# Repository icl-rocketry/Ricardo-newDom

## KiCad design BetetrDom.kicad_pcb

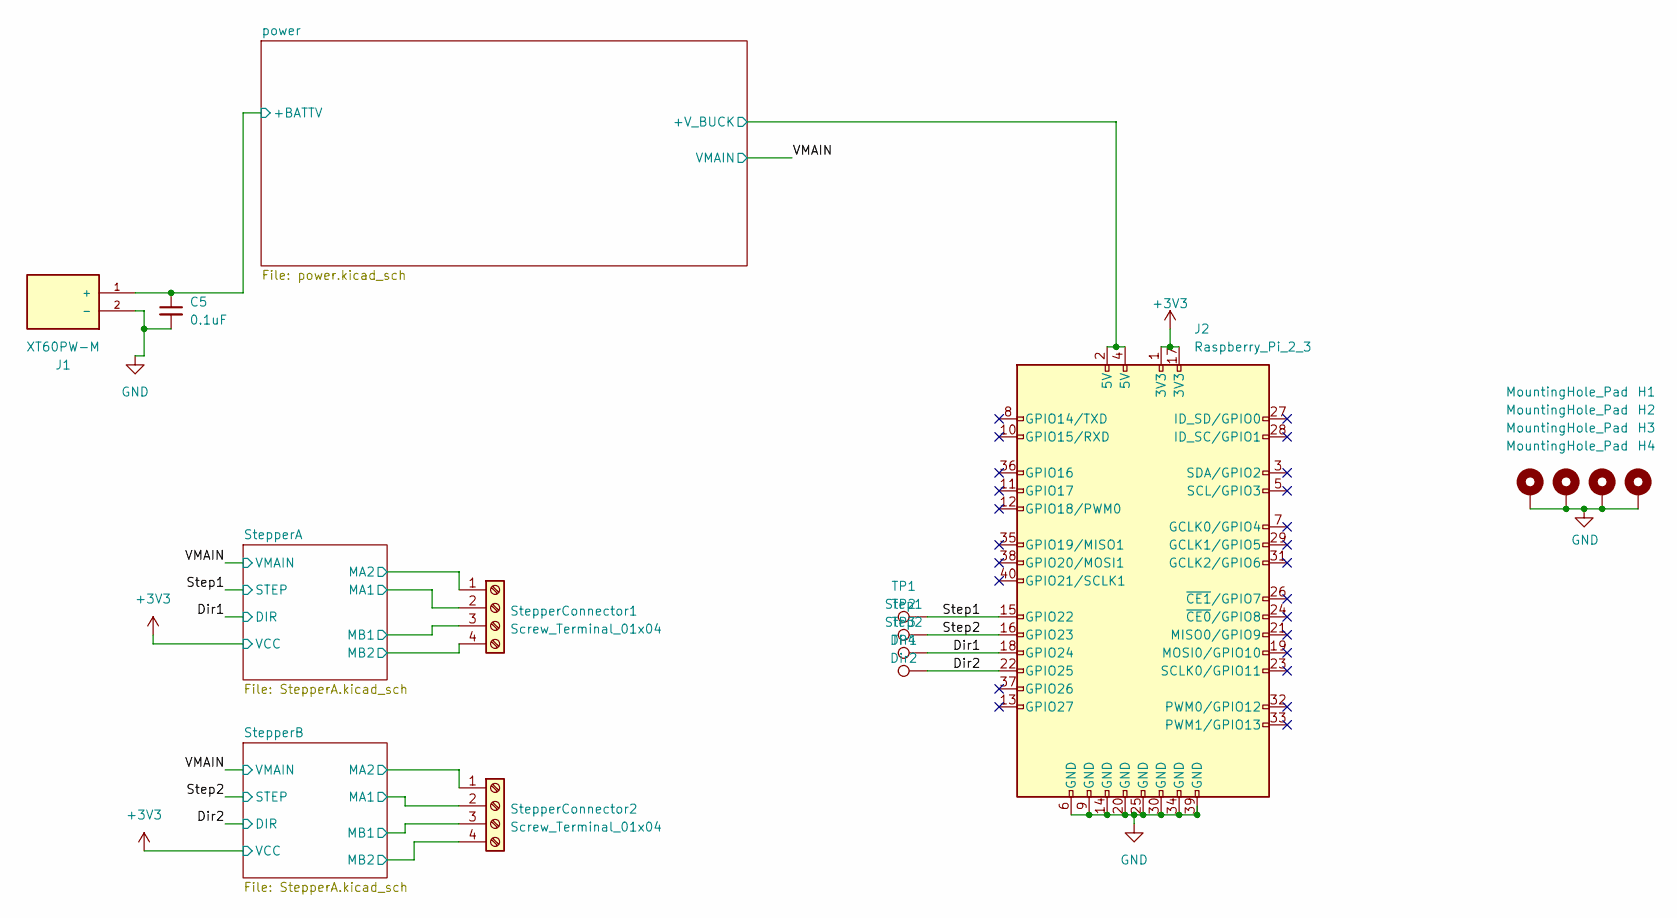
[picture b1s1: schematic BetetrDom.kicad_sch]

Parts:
C5: 0.1uF; C_0402_1005Metric
H1, H2, H3, H4: MountingHole_Pad; MountingHole_3.2mm_M3_DIN965_Pad
J1: XT60PW-M; AMASS_XT60PW-M; PARTREV V1.2
J2: Raspberry_Pi_2_3; PinSocket_2x20_P2.54mm_Vertical
StepperConnector1, StepperConnector2: Screw_Terminal_01x04; Molex_Nano-Fit_105313-xx04_1x04_P2.50mm_Horizontal
TP1: Step1; TestPoint_Pad_1.5x1.5mm
TP2: Step2; TestPoint_Pad_1.5x1.5mm
TP3: Dir1; TestPoint_Pad_1.5x1.5mm
TP4: Dir2; TestPoint_Pad_1.5x1.5mm

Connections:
+3V3: J2.1 (3V3), J2.17 (3V3); also elsewhere on the board
/Dir1: J2.18 (GPIO24), TP3.1; also elsewhere on the board
/Dir2: J2.22 (GPIO25), TP4.1; also elsewhere on the board
/Step1: J2.15 (GPIO22), TP1.1; also elsewhere on the board
/Step2: J2.16 (GPIO23), TP2.1; also elsewhere on the board
/StepperA/MA1: StepperConnector1.2; also elsewhere on the board
/StepperA/MA2: StepperConnector1.1; also elsewhere on the board
/StepperA/MB1: StepperConnector1.3; also elsewhere on the board
/StepperA/MB2: StepperConnector1.4; also elsewhere on the board
/StepperB/MA1: StepperConnector2.2; also elsewhere on the board
/StepperB/MA2: StepperConnector2.1; also elsewhere on the board
/StepperB/MB1: StepperConnector2.3; also elsewhere on the board
/StepperB/MB2: StepperConnector2.4; also elsewhere on the board
/power/+BATTV: C5.1, J1.1 (+); also elsewhere on the board
/power/+V_BUCK: J2.2 (5V), J2.4 (5V); also elsewhere on the board
GND: C5.2, H1.1, H2.1, H3.1, H4.1, J1.2 (-), J2.6 (GND), J2.9 (GND), J2.14 (GND), J2.20 (GND), J2.25 (GND), J2.30 (GND), J2.34 (GND), J2.39 (GND); also elsewhere on the board

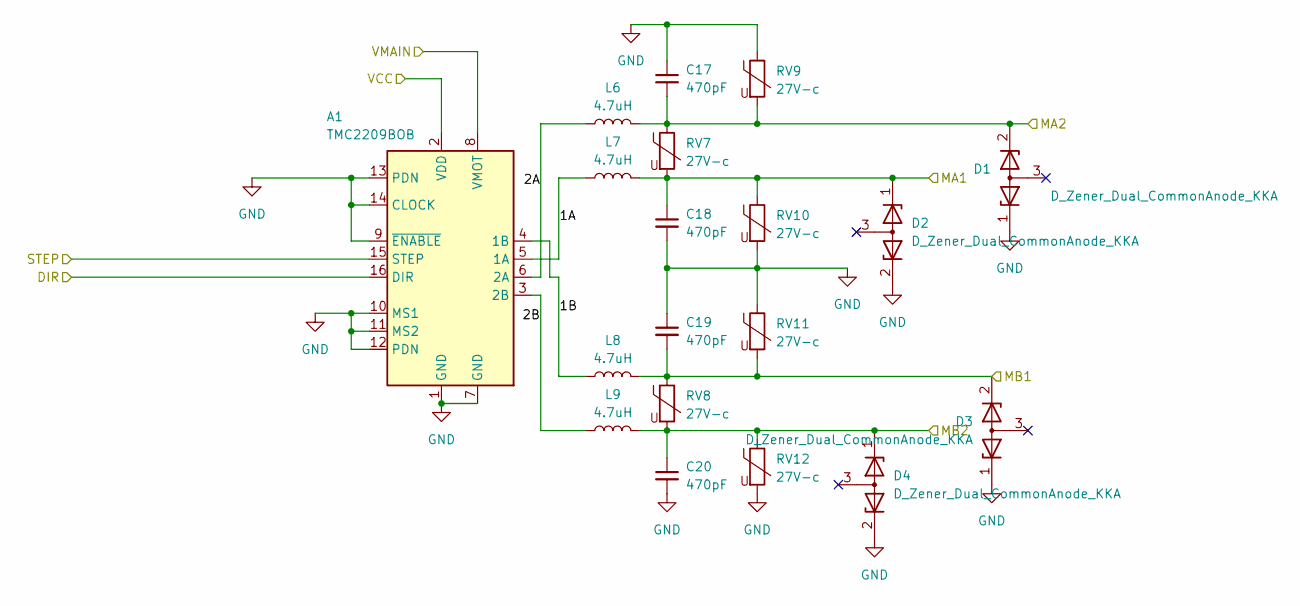
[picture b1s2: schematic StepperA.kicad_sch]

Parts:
A1: TMC2209BOB; Pololu_Breakout-16_15.2x20.3mm
C17, C18, C19, C20: 470pF; C_0603_1608Metric
D1, D2, D3, D4: D_Zener_Dual_CommonAnode_KKA; TSOT-23
L6, L7, L8, L9: 4.7uH; MPLAL60504R7
RV7, RV8, RV9, RV10, RV11, RV12: 27V-c; R_0805_2012Metric

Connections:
+3V3: A1.2 (VDD); also elsewhere on the board
/Dir1: A1.16 (DIR); also elsewhere on the board
/Step1: A1.15 (STEP); also elsewhere on the board
/StepperA/1A: A1.5 (1A), L7.1
/StepperA/1B: A1.4 (1B), L8.1
/StepperA/2A: A1.6 (2A), L6.1
/StepperA/2B: A1.3 (2B), L9.1
/StepperA/MA1: C18.1, D2.1 (K), L7.2, RV7.2, RV10.1; also elsewhere on the board
/StepperA/MA2: C17.2, D1.2 (K), L6.2, RV7.1, RV9.2; also elsewhere on the board
/StepperA/MB1: C19.2, D3.2 (K), L8.2, RV8.1, RV11.2; also elsewhere on the board
/StepperA/MB2: C20.1, D4.1 (K), L9.2, RV8.2, RV12.1; also elsewhere on the board
GND: A1.1 (GND), A1.7 (GND), A1.9 (~ENABLE), A1.10 (MS1), A1.11 (MS2), A1.12 (PDN), A1.13 (PDN), A1.14 (CLOCK), C17.1, C18.2, C19.1, C20.2, D1.1 (K), D2.2 (K), D3.1 (K), D4.2 (K), RV9.1, RV10.2, RV11.1, RV12.2; also elsewhere on the board
VMAIN: A1.8 (VMOT); also elsewhere on the board

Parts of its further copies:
A2: TMC2209BOB; Pololu_Breakout-16_15.2x20.3mm
C13, C14, C15, C16: 470pF; C_0603_1608Metric
D5, D6, D7, D8: D_Zener_Dual_CommonAnode_KKA; TSOT-23
L2, L3, L4, L5: 4.7uH; MPLAL60504R7
RV1, RV2, RV3, RV4, RV5, RV6: 27V-c; R_0805_2012Metric

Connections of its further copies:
+3V3: A2.2 (VDD); also elsewhere on the board
/Dir2: A2.16 (DIR); also elsewhere on the board
/Step2: A2.15 (STEP); also elsewhere on the board
/StepperB/1A: A2.5 (1A), L3.1
/StepperB/1B: A2.4 (1B), L4.1
/StepperB/2A: A2.6 (2A), L2.1
/StepperB/2B: A2.3 (2B), L5.1
/StepperB/MA1: C14.1, D6.1 (K), L3.2, RV1.2, RV4.1; also elsewhere on the board
/StepperB/MA2: C13.2, D5.2 (K), L2.2, RV1.1, RV3.2; also elsewhere on the board
/StepperB/MB1: C15.2, D7.2 (K), L4.2, RV2.1, RV5.2; also elsewhere on the board
/StepperB/MB2: C16.1, D8.1 (K), L5.2, RV2.2, RV6.1; also elsewhere on the board
GND: A2.1 (GND), A2.7 (GND), A2.9 (~ENABLE), A2.10 (MS1), A2.11 (MS2), A2.12 (PDN), A2.13 (PDN), A2.14 (CLOCK), C13.1, C14.2, C15.1, C16.2, D5.1 (K), D6.2 (K), D7.1 (K), D8.2 (K), RV3.1, RV4.2, RV5.1, RV6.2; also elsewhere on the board
VMAIN: A2.8 (VMOT); also elsewhere on the board

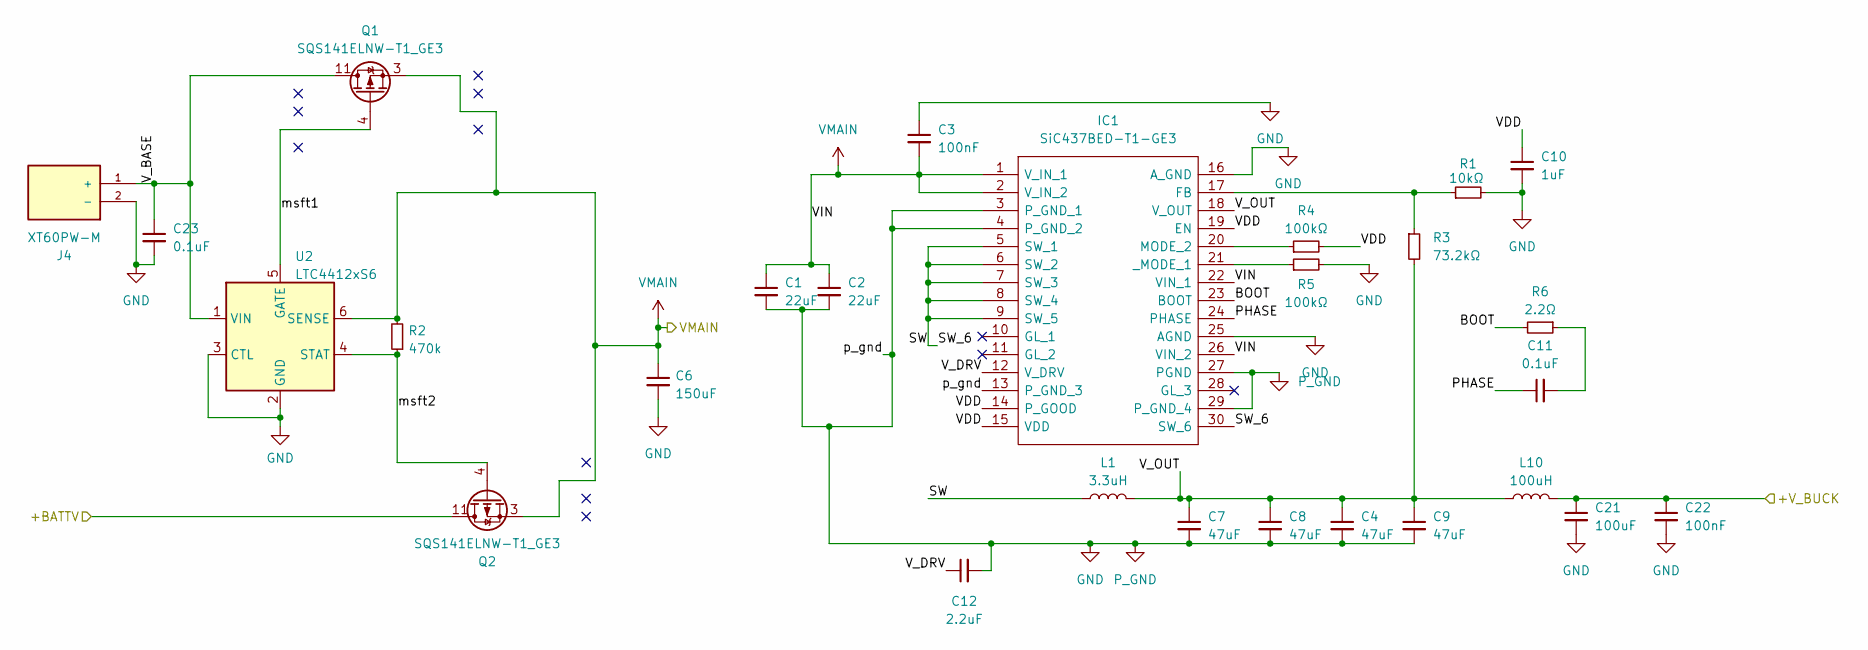
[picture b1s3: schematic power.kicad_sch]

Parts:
C1, C2: 22uF; C_0805_2012Metric
C3, C22: 100nF; C_0402_1005Metric
C4, C7, C8, C9: 47uF; C_1206_3216Metric
C6: 150uF; C_Elec_8x10.2
C10: 1uF; C_0402_1005Metric
C11, C23: 0.1uF; C_0402_1005Metric
C12: 2.2uF; C_0402_1005Metric
C21: 100uF; CP_Elec_10x10
IC1: SiC437BED-T1-GE3; SiC437BEDT1GE3; Manufacturer_Part_Number SiC437BED-T1-GE3; Mouser Part Number 78-SIC437BED-T1-GE3
J4: XT60PW-M; AMASS_XT60PW-M; PARTREV V1.2
L1: 3.3uH; IND_SPM10065VT-3R3M-D
L10: 100uH; SDR1307A101K
Q1, Q2: SQS141ELNW-T1_GE3; SQS850ENT1_GE3; Manufacturer_Part_Number SQS141ELNW-T1_GE3; Mouser Part Number 78-SQS141ELNW-T1_GE3
R1: 10kΩ; R_0402_1005Metric
R2: 470k; R_0603_1608Metric
R3: 73.2kΩ; R_1206_3216Metric
R4, R5: 100kΩ; R_0402_1005Metric
R6: 2.2Ω; R_0402_1005Metric
U2: LTC4412xS6; TSOT-23-6

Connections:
/power/+BATTV: Q2.5, Q2.6, Q2.7, Q2.8, Q2.9, Q2.10, Q2.11; also elsewhere on the board
/power/+V_BUCK: C21.1, C22.1, L10.2; also elsewhere on the board
/power/BOOT: IC1.23 (BOOT), R6.2
/power/PHASE: C11.1, IC1.24 (PHASE)
/power/SW: IC1.5 (SW_1), IC1.6 (SW_2), IC1.7 (SW_3), IC1.8 (SW_4), IC1.9 (SW_5), IC1.30 (SW_6), L1.1
/power/VDD: C10.1, IC1.14 (P_GOOD), IC1.15 (VDD), IC1.19 (EN), R4.2
/power/V_BASE: C23.1, J4.1 (+), Q1.5, Q1.6, Q1.7, Q1.8, Q1.9, Q1.10, Q1.11, U2.1 (VIN)
/power/V_DRV: C12.1, IC1.12 (V_DRV)
/power/V_OUT: C4.1, C7.1, C8.1, C9.1, IC1.18 (V_OUT), L1.2, L10.1, R3.2
/power/msft1: Q1.4, U2.5 (GATE)
/power/msft2: Q2.4, R2.1, U2.4 (STAT)
GND: C1.2, C2.2, C3.1, C4.2, C6.2, C7.2, C8.2, C9.2, C10.2, C12.2, C21.2, C22.2, C23.2, IC1.3 (P_GND_1), IC1.4 (P_GND_2), IC1.13 (P_GND_3), IC1.16 (A_GND), IC1.25 (AGND), IC1.27 (PGND), IC1.29 (P_GND_4), J4.2 (-), R1.2, R5.2, U2.2 (GND), U2.3 (CTL); also elsewhere on the board
unnamed: C11.2, R6.1
unnamed: IC1.17 (FB), R1.1, R3.1
unnamed: IC1.20 (MODE_2), R4.1
unnamed: IC1.21 (_MODE_1), R5.1
VMAIN: C1.1, C2.1, C3.2, C6.1, IC1.1 (V_IN_1), IC1.2 (V_IN_2), IC1.22 (VIN_1), IC1.26 (VIN_2), Q1.1, Q1.2, Q1.3, Q2.1, Q2.2, Q2.3, R2.2, U2.6 (SENSE); also elsewhere on the board

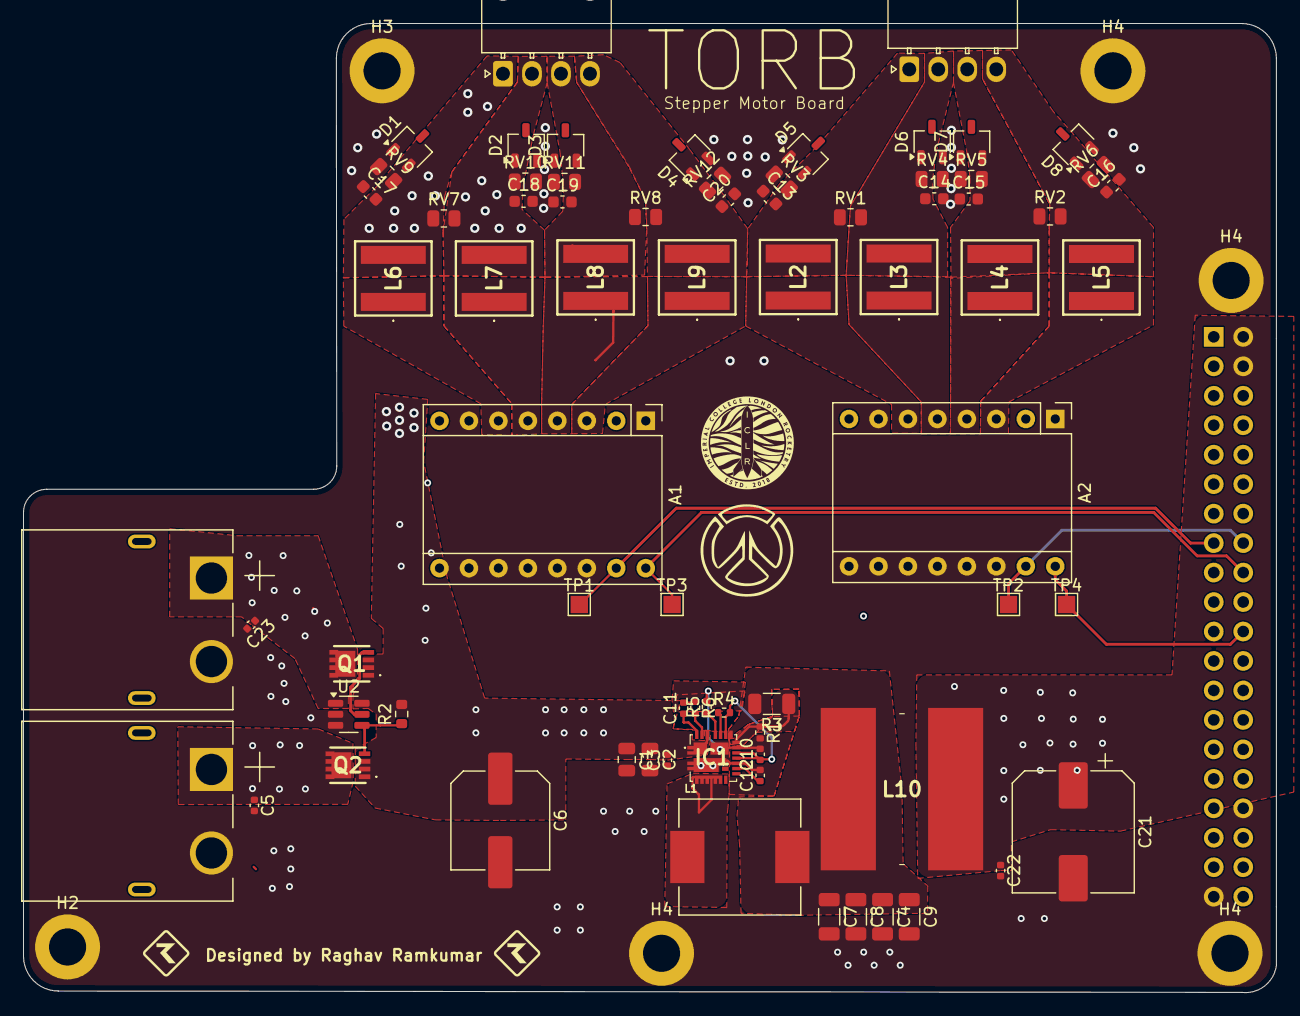
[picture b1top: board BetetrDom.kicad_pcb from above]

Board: 4 copper layers, 108.0 x 83.5 mm, 80 parts (1 on the bottom side), 38 nets.

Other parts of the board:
H4#2, H4#3, H4#4: MountingHole_Pad; MountingHole_3.2mm_M3_DIN965_Pad

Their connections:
GND: H4#2.1, H4#3.1, H4#4.1; also elsewhere on the board

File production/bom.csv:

Designator,Footprint,Quantity,Value,LCSC Part #
"A1, A2",Pololu_Breakout-16_15.2x20.3mm,2,TMC2209BOB,
"C1, C2",0805,2,22uF,
C10,0402,1,1uF,
"C11, C23, C5",0402,3,0.1uF,
C12,0402,1,2.2uF,
"C13, C14, C15, C16, C17, C18, C19, C20",0603,8,470pF,
C21,CP_Elec_10x10,1,100uF,
"C22, C3",0402,2,100nF,
"C4, C7, C8, C9",1206,4,47uF,
C6,C_Elec_8x10.2,1,150uF,
"D1, D2, D3, D4, D5, D6, D7, D8",TSOT-23,8,D_Zener_Dual_CommonAnode_KKA,
"H1, H2, H3, H4",MountingHole_3.2mm_M3_DIN965_Pad,4,MountingHole_Pad,
IC1,SiC437BEDT1GE3,1,SiC437BED-T1-GE3,
"J1, J4",AMASS_XT60PW-M,2,XT60PW-M,
J2,PinSocket_2x20_P2.54mm_Vertical,1,Raspberry_Pi_2_3,
L1,1008,1,1.5uH,
L10,SDR1307A101K,1,100uH,
"L2, L3, L4, L5, L6, L7, L8, L9",0603,8,80nH,
"Q1, Q2",PXP01230QLJ,2,PXP012-30QLJ,
R1,0402,1,10kΩ,
R2,0603,1,470k,
R3,1206,1,73.2kΩ,
"R4, R5",0402,2,100kΩ,
R6,0402,1,2.2Ω,
"RV1, RV10, RV11, RV12, RV2, RV3, RV4, RV5, RV6, RV7, RV8, RV9",0805,12,27V-c,
"StepperConnector1, StepperConnector2",Molex_Nano-Fit_105313-xx04_1x04_P2.50mm_Horizontal,2,Screw_Terminal_01x04,
TP1,TestPoint_Pad_1.5x1.5mm,1,Step1,
TP2,TestPoint_Pad_1.5x1.5mm,1,Step2,
TP3,TestPoint_Pad_1.5x1.5mm,1,Dir1,
TP4,TestPoint_Pad_1.5x1.5mm,1,Dir2,
U2,TSOT-23-6,1,LTC4412xS6,

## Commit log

2024-09-06 first circuit andrei pls be ncie
2024-09-06 with ports for steppers
2024-09-09 added zener diodes
2024-09-10 update 2 everything is fixed
2024-09-10 ideal diode update to be checked
2024-09-10 update again
2024-09-19 finished pcb layouts, ready for check p sure
2024-09-19 no message
2024-09-23 uodate
2024-10-02 update-i hate babs
2024-10-02 babs (barbara) jeng
2024-10-02 fuck it baseball hat
2024-10-02 donedonedone
2024-10-02 newnewnew
